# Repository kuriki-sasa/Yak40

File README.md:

# Yak40
Yak40 is an Alice-like Keyboard

## Dependent libraries
- CadQuery
  https://pypi.org/project/cadquery/
- CQ-Kit
  https://pypi.org/project/cqkit/
- NumPy
  https://pypi.org/project/numpy/
- SciPy
  https://pypi.org/project/scipy/
- pykle_serial
  https://github.com/hajimen/pykle_serial

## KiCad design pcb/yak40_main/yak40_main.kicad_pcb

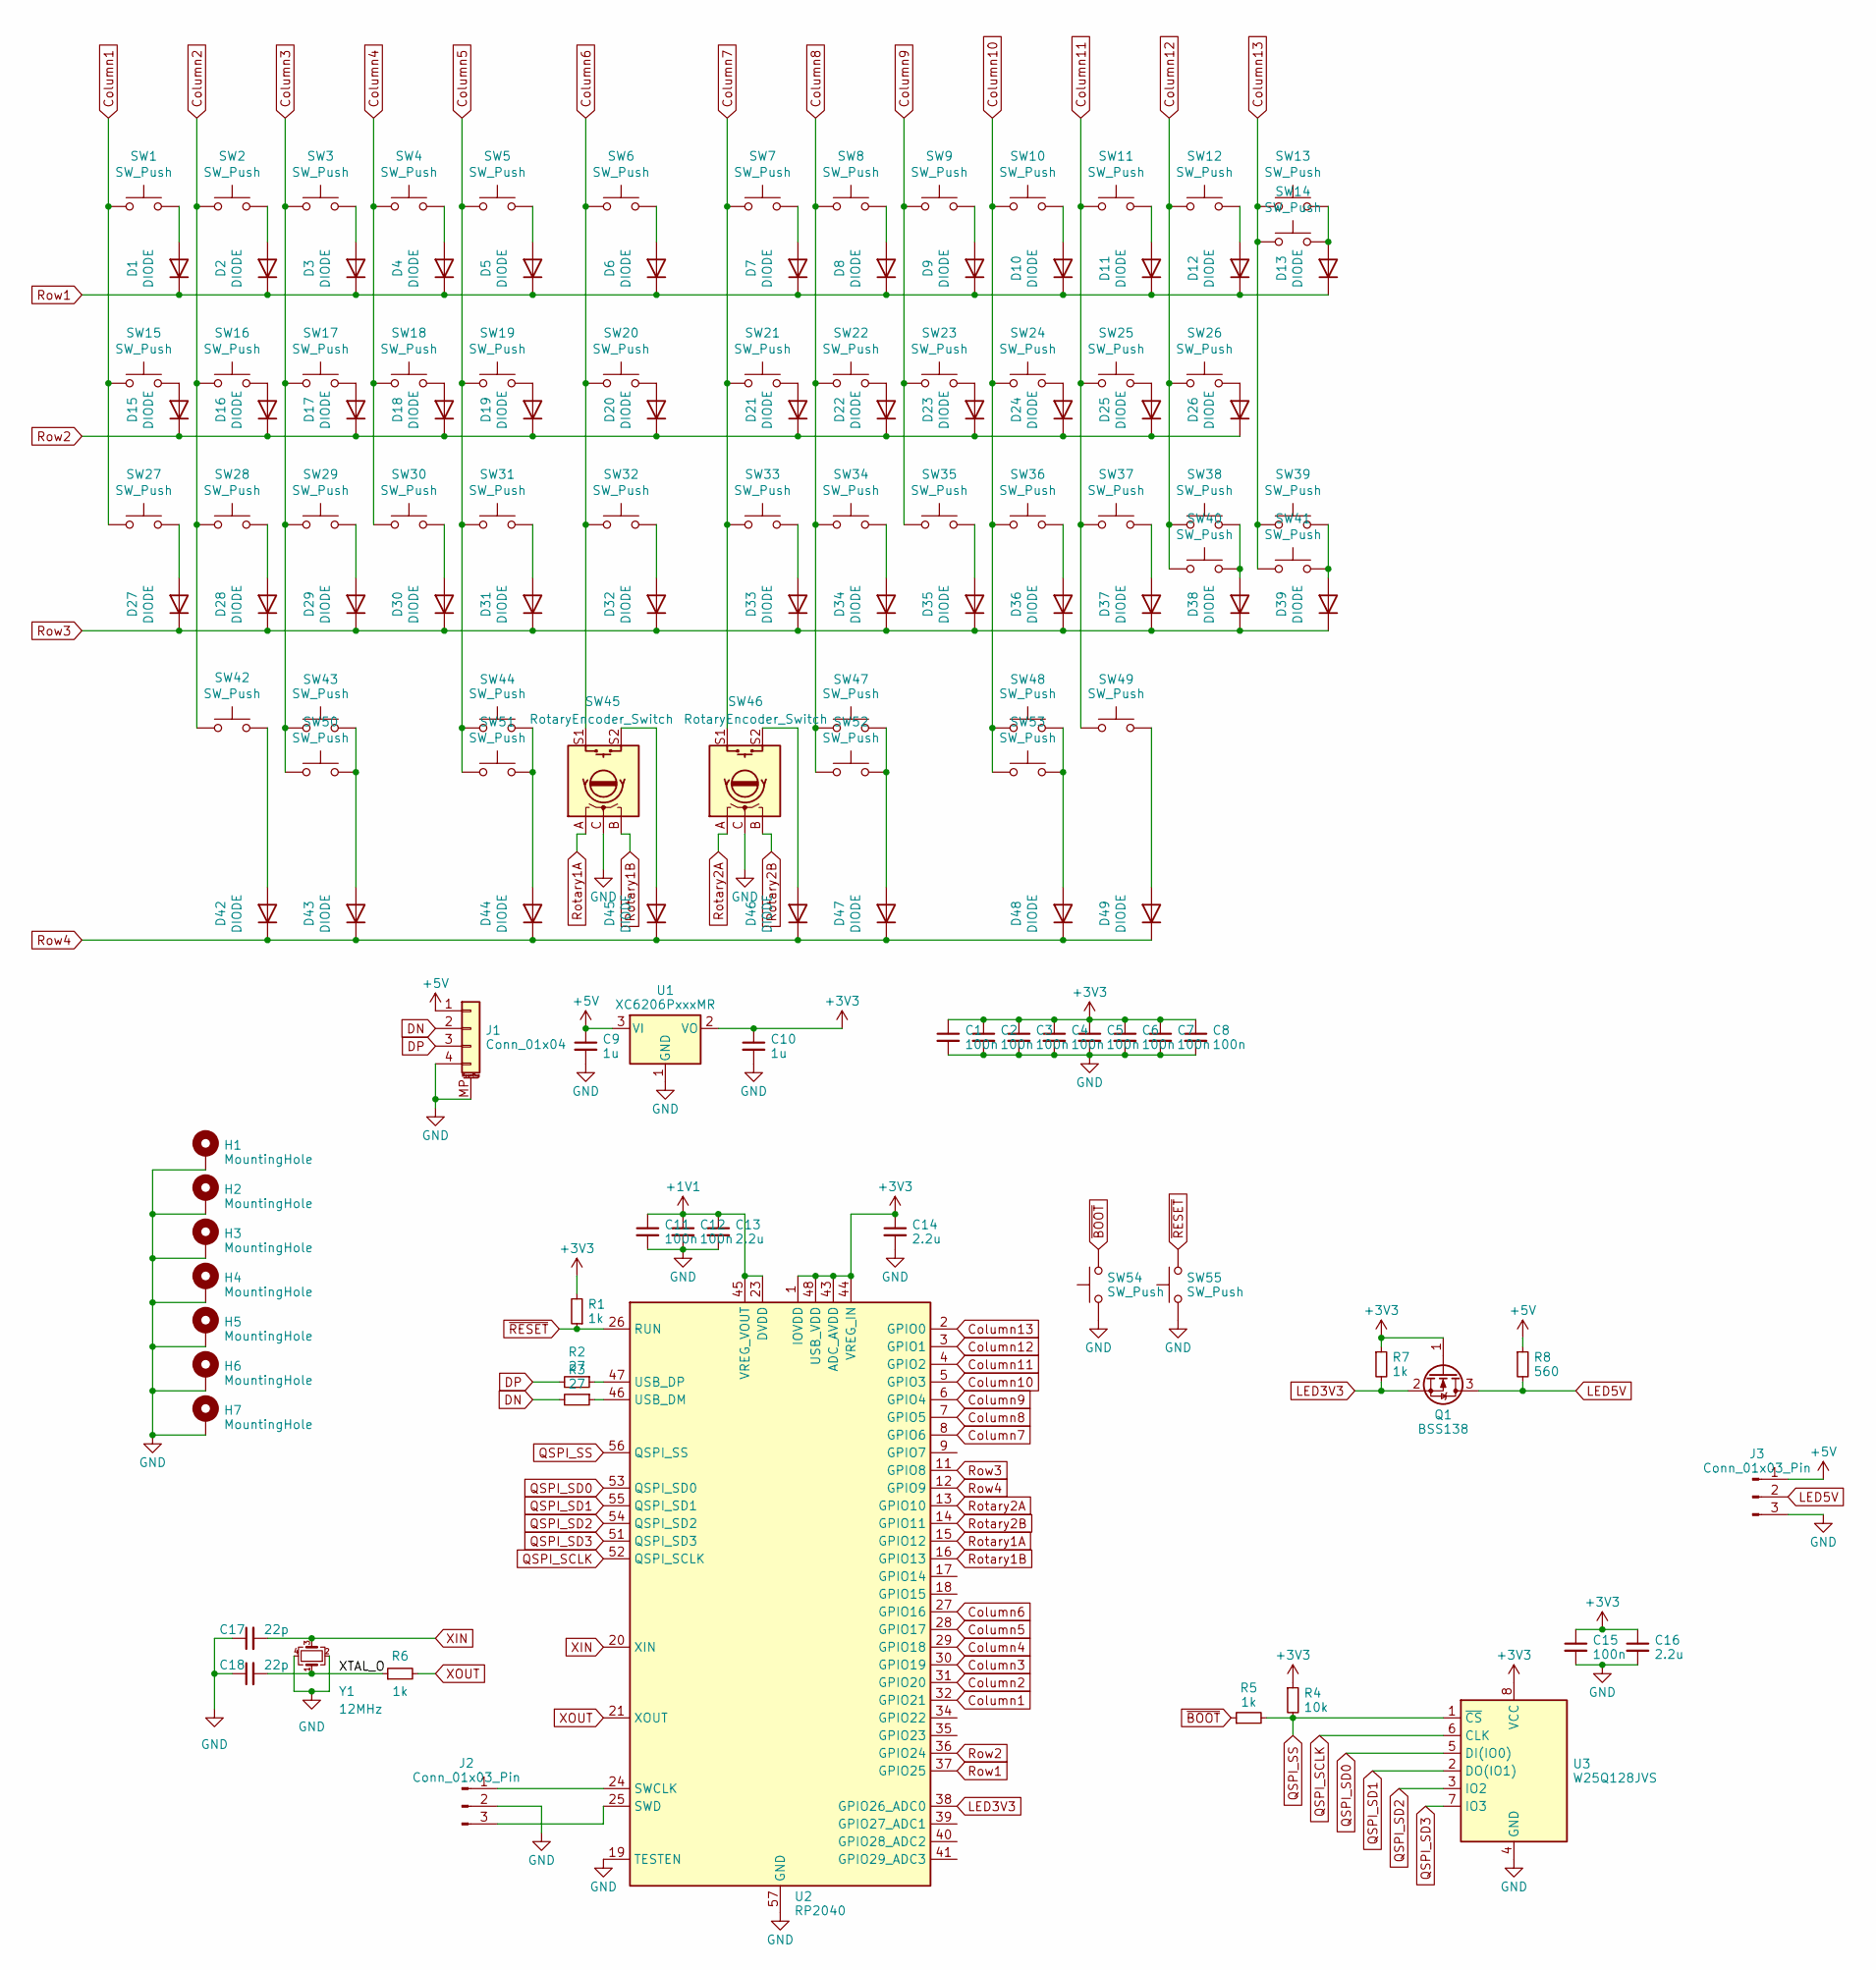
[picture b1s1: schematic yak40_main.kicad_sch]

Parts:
C1, C2, C3, C4, C5, C6, C7, C8, C11, C12, C15: 100n; C_0402_1005Metric
C9, C10: 1u; C_0402_1005Metric
C13, C14, C16: 2.2u; C_0402_1005Metric
C17, C18: 22p; C_0402_1005Metric; LCSC C1555
D1, D2, D3, D4, D5, D6, D7, D8, D9, D10, D11, D12, D13, D15, D16, D17, D18, D19, D20, D21, D22, D23, D24, D25, D26, D27, D28, D29, D30, D31, D32, D33, D34, D35, D36, D37, D38, D39, D42, D43, D44, D45, D46, D47, D48, D49: DIODE; D_SOD-123
H1, H2, H3, H4, H5, H6, H7: MountingHole; MountingHole_2.2mm_M2_ISO7380_Pad
J1: Conn_01x04; Molex_Pico-EZmate_78171-0004_1x04-1MP_P1.20mm_Vertical
J2, J3: Conn_01x03_Pin; PinHeader_1x03_P2.54mm_Vertical
Q1: BSS138; SOT-23
R1, R5, R7: 1k; R_0402_1005Metric
R2, R3: 27; R_0402_1005Metric
R4: 10k; R_0402_1005Metric
R6: 1k; R_0402_1005Metric; LCSC C11702
R8: 560; R_0603_1608Metric
SW1, SW2, SW3, SW4, SW5, SW6, SW7, SW8, SW9, SW10, SW11, SW12, SW13, SW16, SW17, SW18, SW19, SW20, SW21, SW22, SW23, SW24, SW25, SW28, SW29, SW30, SW31, SW32, SW33, SW34, SW35, SW36, SW37, SW39, SW40: SW_Push; MX-Hotswap-1U
SW14, SW44, SW47: SW_Push; MX-Hotswap-2U
SW15, SW38, SW41, SW43, SW48: SW_Push; MX-Hotswap-1.25U
SW26, SW27: SW_Push; MX-Hotswap-1.75U
SW42, SW49, SW50, SW53: SW_Push; MX-Hotswap-1.5U
SW45, SW46: RotaryEncoder_Switch; SW_Cherry_MX_1.00u_Kailh_EC12
SW51, SW52: SW_Push; MX-Hotswap-2.75U
SW54, SW55: SW_Push; SW_Push_1P1T_XKB_TS-1187A
U1: XC6206PxxxMR; SOT-23-3
U2: RP2040; QFN-56-1EP_7x7mm_P0.4mm_EP3.2x3.2mm
U3: W25Q128JVS; SOIC-8_5.23x5.23mm_P1.27mm
Y1: 12MHz; Crystal_SMD_3225-4Pin_3.2x2.5mm; LCSC C9002

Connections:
+1V1: C11.1, C12.1, C13.1, U2.23 (DVDD), U2.45 (VREG_VOUT), U2.50 (DVDD)
+3V3: C1.1, C2.1, C3.1, C4.1, C5.1, C6.1, C7.1, C8.1, C10.1, C14.1, C15.1, C16.1, Q1.1 (G), R1.2, R4.1, R7.1, U1.2 (VO), U2.1 (IOVDD), U2.10 (IOVDD), U2.22 (IOVDD), U2.33 (IOVDD), U2.42 (IOVDD), U2.43 (ADC_AVDD), U2.44 (VREG_IN), U2.48 (USB_VDD), U2.49 (IOVDD), U3.8 (VCC)
+5V: C9.1, J1.1, J3.1, R8.1, U1.3 (VI)
/XTAL_O: C18.2, R6.1, Y1.1
Column1: SW1.1, SW15.1, SW27.1, U2.32 (GPIO21)
Column2: SW2.1, SW16.1, SW28.1, SW42.1, U2.31 (GPIO20)
Column3: SW3.1, SW17.1, SW29.1, SW43.1, SW50.1, U2.30 (GPIO19)
Column4: SW4.1, SW18.1, SW30.1, U2.29 (GPIO18)
Column5: SW5.1, SW19.1, SW31.1, SW44.1, SW51.1, U2.28 (GPIO17)
Column6: SW6.1, SW20.1, SW32.1, SW45.S1, U2.27 (GPIO16)
Column7: SW7.1, SW21.1, SW33.1, SW46.S1, U2.8 (GPIO6)
Column8: SW8.1, SW22.1, SW34.1, SW47.1, SW52.1, U2.7 (GPIO5)
Column9: SW9.1, SW23.1, SW35.1, U2.6 (GPIO4)
Column10: SW10.1, SW24.1, SW36.1, SW48.1, SW53.1, U2.5 (GPIO3)
Column11: SW11.1, SW25.1, SW37.1, SW49.1, U2.4 (GPIO2)
Column12: SW12.1, SW26.1, SW38.1, SW40.1, U2.3 (GPIO1)
Column13: SW13.1, SW14.1, SW39.1, SW41.1, U2.2 (GPIO0)
DN: J1.2, R3.2
DP: J1.3, R2.2
GND: C1.2, C2.2, C3.2, C4.2, C5.2, C6.2, C7.2, C8.2, C9.2, C10.2, C11.2, C12.2, C13.2, C14.2, C15.2, C16.2, C17.1, C18.1, H1.1, H2.1, H3.1, H4.1, H5.1, H6.1, H7.1, J1.4, J1.MP (MountPin), J2.2, J3.3, SW45.C, SW46.C, SW54.1, SW55.1, U1.1 (GND), U2.19 (TESTEN), U2.57 (GND), U3.4 (GND), Y1.2, Y1.4
LED3V3: Q1.2 (S), R7.2, U2.38 (GPIO26_ADC0)
LED5V: J3.2, Q1.3 (D), R8.2
unnamed: D1.2 (A), SW1.2
unnamed: D2.2 (A), SW2.2
unnamed: D3.2 (A), SW3.2
unnamed: D4.2 (A), SW4.2
unnamed: D5.2 (A), SW5.2
unnamed: D6.2 (A), SW6.2
unnamed: D7.2 (A), SW7.2
unnamed: D8.2 (A), SW8.2
unnamed: D9.2 (A), SW9.2
unnamed: D10.2 (A), SW10.2
unnamed: D11.2 (A), SW11.2
unnamed: D12.2 (A), SW12.2
unnamed: D13.2 (A), SW13.2, SW14.2
unnamed: D15.2 (A), SW15.2
unnamed: D16.2 (A), SW16.2
unnamed: D17.2 (A), SW17.2
unnamed: D18.2 (A), SW18.2
unnamed: D19.2 (A), SW19.2
unnamed: D20.2 (A), SW20.2
unnamed: D21.2 (A), SW21.2
unnamed: D22.2 (A), SW22.2
unnamed: D23.2 (A), SW23.2
unnamed: D24.2 (A), SW24.2
unnamed: D25.2 (A), SW25.2
unnamed: D26.2 (A), SW26.2
unnamed: D27.2 (A), SW27.2
unnamed: D28.2 (A), SW28.2
unnamed: D29.2 (A), SW29.2
unnamed: D30.2 (A), SW30.2
unnamed: D31.2 (A), SW31.2
unnamed: D32.2 (A), SW32.2
unnamed: D33.2 (A), SW33.2
unnamed: D34.2 (A), SW34.2
unnamed: D35.2 (A), SW35.2
unnamed: D36.2 (A), SW36.2
unnamed: D37.2 (A), SW37.2
unnamed: D38.2 (A), SW38.2, SW40.2
unnamed: D39.2 (A), SW39.2, SW41.2
unnamed: D42.2 (A), SW42.2
unnamed: D43.2 (A), SW43.2, SW50.2
unnamed: D44.2 (A), SW44.2, SW51.2
unnamed: D45.2 (A), SW45.S2
unnamed: D46.2 (A), SW46.S2
unnamed: D47.2 (A), SW47.2, SW52.2
unnamed: D48.2 (A), SW48.2, SW53.2
unnamed: D49.2 (A), SW49.2
unnamed: J2.1, U2.24 (SWCLK)
unnamed: J2.3, U2.25 (SWD)
unnamed: R3.1, U2.46 (USB_DM)
unnamed: R2.1, U2.47 (USB_DP)
QSPI_SCLK: U2.52 (QSPI_SCLK), U3.6 (CLK)
QSPI_SD0: U2.53 (QSPI_SD0), U3.5 (DI(IO0))
QSPI_SD1: U2.55 (QSPI_SD1), U3.2 (DO(IO1))
QSPI_SD2: U2.54 (QSPI_SD2), U3.3 (IO2)
QSPI_SD3: U2.51 (QSPI_SD3), U3.7 (IO3)
QSPI_SS: R4.2, R5.2, U2.56 (QSPI_SS), U3.1 (~CS)
Rotary1A: SW45.A, U2.15 (GPIO12)
Rotary1B: SW45.B, U2.16 (GPIO13)
Rotary2A: SW46.A, U2.13 (GPIO10)
Rotary2B: SW46.B, U2.14 (GPIO11)
Row1: D1.1 (K), D2.1 (K), D3.1 (K), D4.1 (K), D5.1 (K), D6.1 (K), D7.1 (K), D8.1 (K), D9.1 (K), D10.1 (K), D11.1 (K), D12.1 (K), D13.1 (K), U2.37 (GPIO25)
Row2: D15.1 (K), D16.1 (K), D17.1 (K), D18.1 (K), D19.1 (K), D20.1 (K), D21.1 (K), D22.1 (K), D23.1 (K), D24.1 (K), D25.1 (K), D26.1 (K), U2.36 (GPIO24)
Row3: D27.1 (K), D28.1 (K), D29.1 (K), D30.1 (K), D31.1 (K), D32.1 (K), D33.1 (K), D34.1 (K), D35.1 (K), D36.1 (K), D37.1 (K), D38.1 (K), D39.1 (K), U2.11 (GPIO8)
Row4: D42.1 (K), D43.1 (K), D44.1 (K), D45.1 (K), D46.1 (K), D47.1 (K), D48.1 (K), D49.1 (K), U2.12 (GPIO9)
XIN: C17.2, U2.20 (XIN), Y1.3
XOUT: R6.2, U2.21 (XOUT)
~BOOT: R5.1, SW54.2
~RESET: R1.1, SW55.2, U2.26 (RUN)

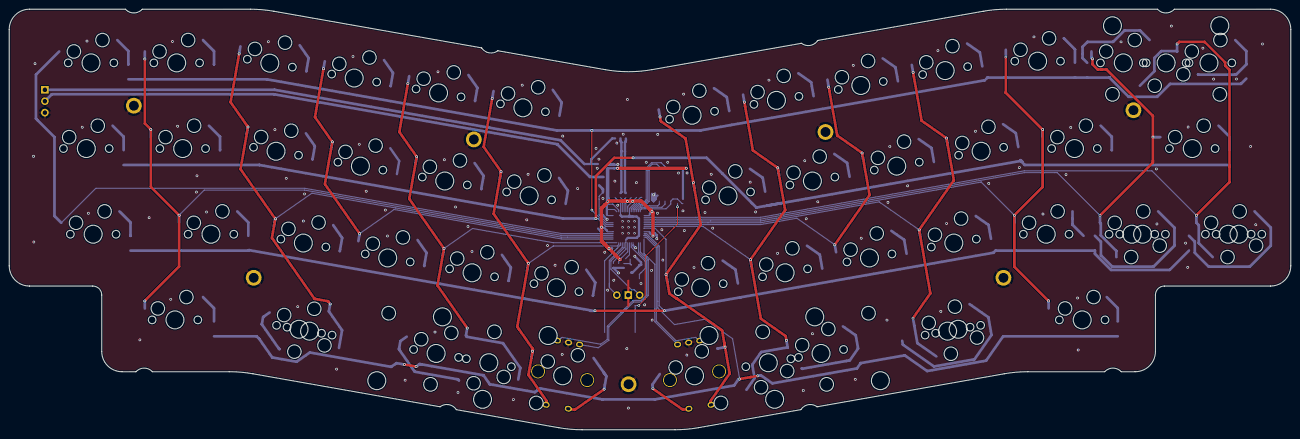
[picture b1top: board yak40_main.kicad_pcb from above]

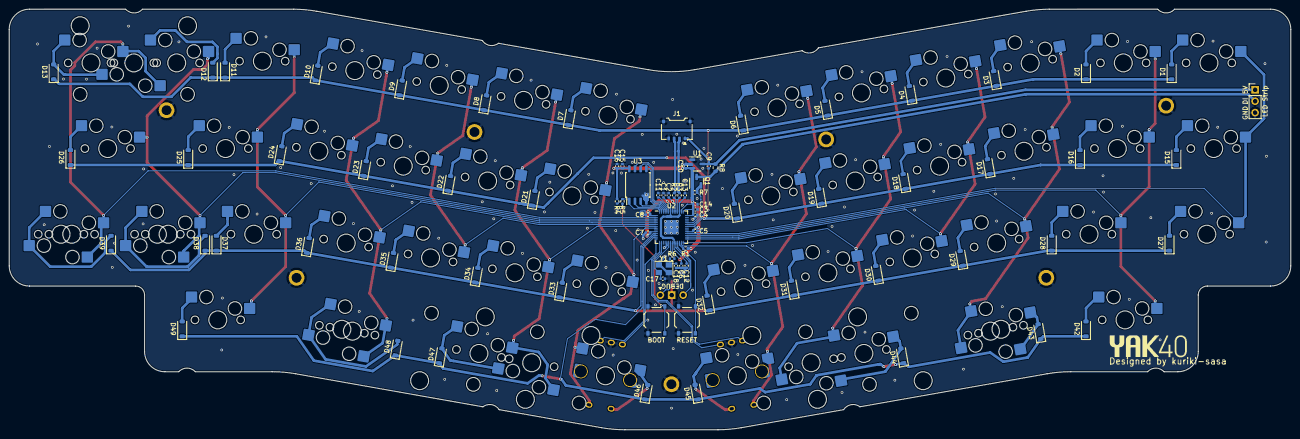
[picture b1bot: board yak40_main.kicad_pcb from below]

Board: 2 copper layers, 285.0 x 93.5 mm, 142 parts (82 on the bottom side), 90 nets.

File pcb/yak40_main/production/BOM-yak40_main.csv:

Comment,Designator,Footprint,LCSC
1k,"R1,R5,R6",R_0402_1005Metric,C11702
2.2u,"C13,C14,C16",C_0402_1005Metric,C12530
100n,"C1,C11,C12,C15,C2,C3,C4,C5,C6,C7,C8",C_0402_1005Metric,C1525
22p,"C17,C18",C_0402_1005Metric,C1555
RP2040,U2,QFN-56-1EP_7x7mm_P0.4mm_EP3.2x3.2mm,C2040
27,"R2,R3",R_0402_1005Metric,C25100
10k,R4,R_0402_1005Metric,C25744
SW_Push,"SW54,SW55",SW_Push_1P1T_XKB_TS-1187A,C318884
Conn_01x04,J1,Molex_Pico-EZmate_78171-0004_1x04-1MP_P1.20mm_Vertical,C528030
1u,"C10,C9",C_0402_1005Metric,C52923
XC6206PxxxMR,U1,SOT-23-3,C5446
DIODE,"D1,D10,D11,D12,D13,D15,D16,D17,D18,D19,D2,D20,D21,D22,D23,D24,D25,D26,D27,D28,D29,D3,D30,D31,D32,D33,D34,D35,D36,D37,D38,D39,D4,D42,D43,D44,D45,D46,D47,D48,D49,D5,D6,D7,D8,D9",D_SOD-123,C81598
12MHz,Y1,Crystal_SMD_3225-4Pin_3.2x2.5mm,C9002
W25Q128JVS,U3,SOIC-8_5.23x5.23mm_P1.27mm,C97521

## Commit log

2023-09-24 Add submodule for key switch footprint
2023-09-24 Add main project
2023-09-25 Add layout files
2023-10-21 Change footprint library for switch to MX_V2
2023-10-21 Rename Layout dir to layout
2023-10-21 Add files for plate
2023-10-21 Wiring footprints
2023-10-21 Rename kicad to pcb
2023-10-21 Change license to THE MIT SUSHI-WARE LICENSE
2023-11-23 [WIP]Add case files
2023-11-23 Remove unnecessary files
2023-11-23 Update layout json
2023-11-29 Add screw holes
2023-11-29 Move STEP/STL files to build directory
2023-11-29 Comment out jupyter
2023-11-29 Fix screw hole depth
2023-11-29 Add 2D drawing
2023-11-29 Rename build to production
2023-11-29 Remove unnecessary file
2023-12-01 Fix depth for o-ring
2023-12-01 Add dxf files for base plate
2023-12-04 Reduct cutting amount
2024-01-03 Update case
2024-01-03 Update pcb
2024-01-03 Update plate
2024-02-02 Update PCB to be cheaper
2024-02-02 Update plate files
2024-02-02 Add foam outline
2024-02-06 Update case files to released version
2024-06-22 Support LED and rotary encoders
2024-07-11 Add empty buildguide
2024-11-08 Add japanese buildguide
2024-11-08 Fix content level
2024-11-08 Fix buildguide
2024-11-08 Fix new-line before images
2024-11-08 Update org file
2024-11-08 Add new-line option
2024-11-08 Fix org file
2024-11-08 Fix build guide
2024-11-08 Test html tag
2024-11-10 Add macro
2024-11-10 Replace org to markdown
2024-11-10 Add description of PCB thickness
2024-11-10 Add english buildguide
2024-11-10 Increase japanese buildguide
2024-11-10 Fix translation omissions
2025-01-12 Add bottom plate files for CNC milling
2025-01-12 Add drawing for laser marking
